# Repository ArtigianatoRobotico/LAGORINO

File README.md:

# LAGORINO
Lagorino is a small didactic robot made in Langhirano (Parma IT) by Stefano Scibilia and developed with the contribute of RoboMakersLab

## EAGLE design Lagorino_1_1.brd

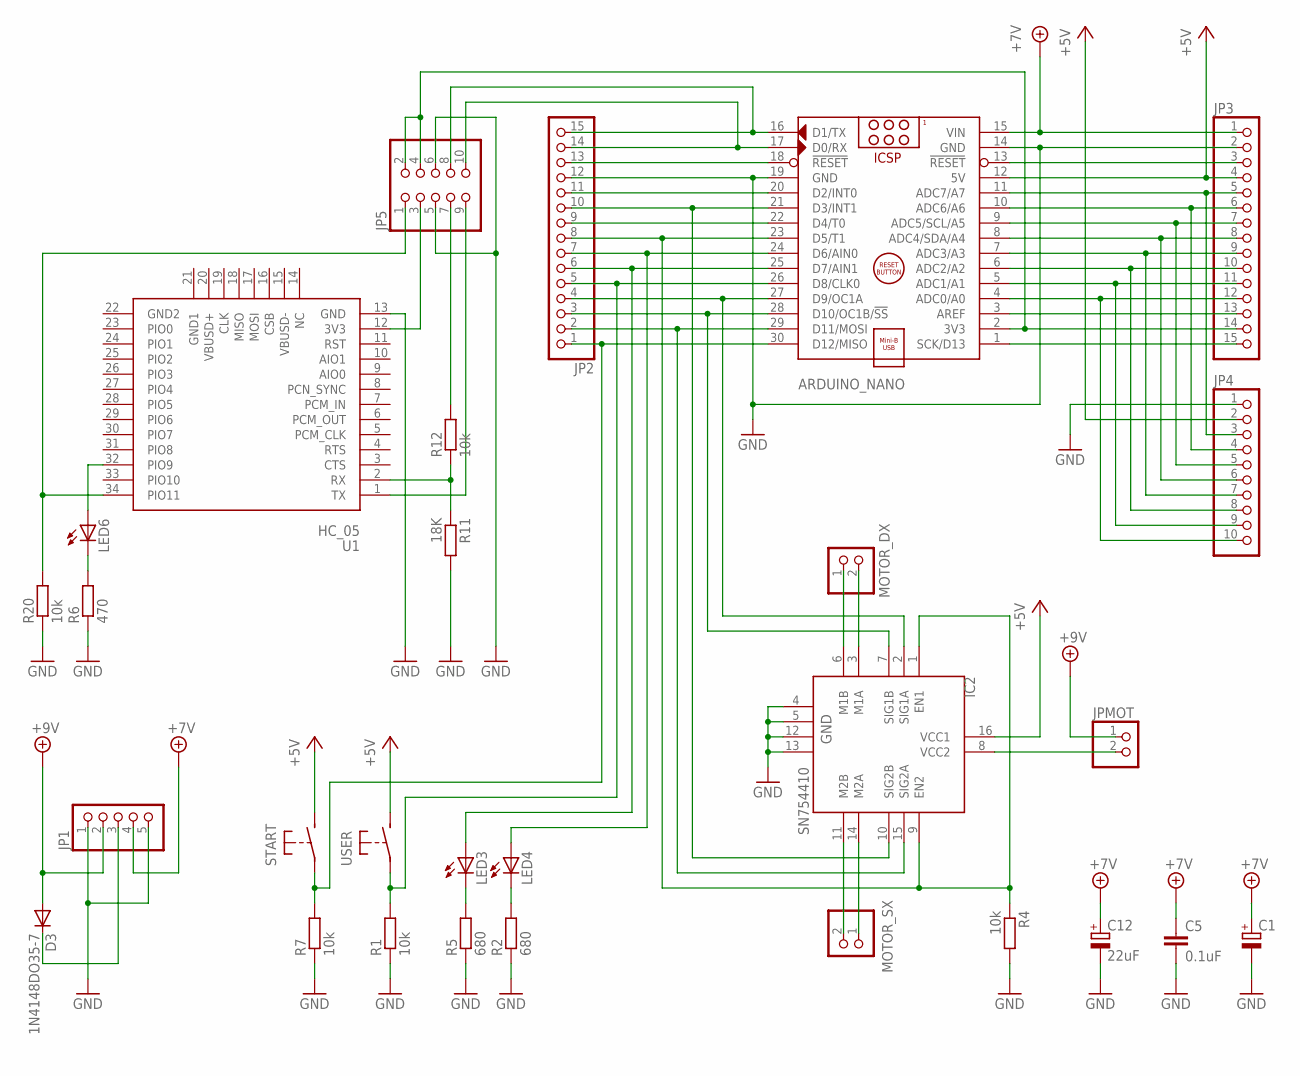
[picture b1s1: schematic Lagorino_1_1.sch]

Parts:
ARDUINO_NANO: ARDUINO_NANO
C1: CPOL-EUE5-6; E5-6
C5: 0.1uF; C0805K
C12: 22uF; A/3216-18W
D3: 1N4148DO35-7; DO35-7
IC2: SN754410; DIP16
JP1: PINHD-1X5; 1X05
JP2, JP3: PINHD-1X15; 1X15
JP4: PINHD-1X10; 1X10
JP5: PINHD-2X5; 2X05
JPMOT: PINHD-1X2; 1X02
LED3, LED4, LED6: LED_E; LED_1206
MOTOR_DX: PINHD-1X2; 1X02
MOTOR_SX: PINHD-1X2; 1X02
R1, R4, R20: 10k; M0805
R2, R5: 680; R0805
R6: 470; R0805
R7, R12: 10k; R0805
R11: 18K; M0805
START: SWITCH-MISC_FSM
U1: HC_05; BLUETOOTH_SMD
USER: SWITCH-MISC_FSM

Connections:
+5V: ARDUINO_NANO.12 (5V), IC2.16 (VCC1), JP3.4, JP4.2, START.P$2 (S), USER.P$2 (S)
+7V: ARDUINO_NANO.15 (VIN), C1.+, C5.1, C12.+, JP1.4, JP3.1
+9V: D3.A, JP1.2, JPMOT.1
GND: ARDUINO_NANO.14 (GND), ARDUINO_NANO.19 (GND), C1.-, C5.2, C12.-, IC2.4, IC2.5, IC2.12, IC2.13, JP1.1, JP1.5, JP2.12, JP3.2, JP4.1, JP5.5, JP5.6, R1.1, R2.1, R4.2, R5.1, R6.1, R7.1, R11.2, R20.1, U1.13 (GND)
unnamed: JP5.7, R12.2
unnamed: JP5.9, U1.1 (TX)
unnamed: IC2.8 (VCC2), JPMOT.2
unnamed: D3.C, JP1.3
unnamed: IC2.6 (M1B), MOTOR_DX.1
unnamed: ARDUINO_NANO.27 (D9/OC1A), IC2.2 (SIG1A), JP2.4
unnamed: ARDUINO_NANO.26 (D8/CLK0), JP2.5, R1.2, USER.P$1
unnamed: ARDUINO_NANO.25 (D7/AIN1), JP2.6, LED3.A
unnamed: ARDUINO_NANO.24 (D6/AIN0), JP2.7, LED4.A
unnamed: IC2.3 (M1A), MOTOR_DX.2
unnamed: ARDUINO_NANO.2 (3V3), JP3.14, JP5.2, JP5.4
unnamed: IC2.11 (M2B), MOTOR_SX.2
unnamed: IC2.14 (M2A), MOTOR_SX.1
unnamed: ARDUINO_NANO.13 (!RESET), JP3.3
unnamed: ARDUINO_NANO.17 (D0/RX), JP2.14, JP5.10
unnamed: ARDUINO_NANO.16 (D1/TX), JP2.15, JP5.8
unnamed: ARDUINO_NANO.29 (D11/MOSI), IC2.15 (SIG2A), JP2.2
unnamed: ARDUINO_NANO.3 (AREF), JP3.13
unnamed: ARDUINO_NANO.11 (ADC7/A7), JP3.5, JP4.3
unnamed: R11.1, R12.1, U1.2 (RX)
unnamed: ARDUINO_NANO.10 (ADC6/A6), JP3.6, JP4.4
unnamed: ARDUINO_NANO.9 (ADC5/SCL/A5), JP3.7, JP4.5
unnamed: ARDUINO_NANO.8 (ADC4/SDA/A4), JP3.8, JP4.6
unnamed: JP5.3, U1.12 (3V3)
unnamed: ARDUINO_NANO.1 (SCK/D13), JP3.15
unnamed: ARDUINO_NANO.7 (ADC3/A3), JP3.9, JP4.7
unnamed: ARDUINO_NANO.6 (ADC2/A2), JP3.10, JP4.8
unnamed: ARDUINO_NANO.5 (ADC1/A1), JP3.11, JP4.9
unnamed: ARDUINO_NANO.4 (ADC0/A0), JP3.12, JP4.10
unnamed: ARDUINO_NANO.18 (!RESET), JP2.13
unnamed: ARDUINO_NANO.20 (D2/INT0), JP2.11
unnamed: LED4.C, R2.2
unnamed: LED3.C, R5.2
unnamed: ARDUINO_NANO.30 (D12/MISO), JP2.1, R7.2, START.P$1
unnamed: ARDUINO_NANO.22 (D4/T0), JP2.9
unnamed: ARDUINO_NANO.21 (D3/INT1), IC2.10 (SIG2B), JP2.10
unnamed: ARDUINO_NANO.28 (D10/OC1B/!SS), IC2.7 (SIG1B), JP2.3
unnamed: ARDUINO_NANO.23 (D5/T1), IC2.1 (EN1), IC2.9 (EN2), JP2.8, R4.1
unnamed: LED6.C, R6.2
unnamed: LED6.A, U1.32 (PIO9)
unnamed: JP5.1, R20.2, U1.34 (PIO11)

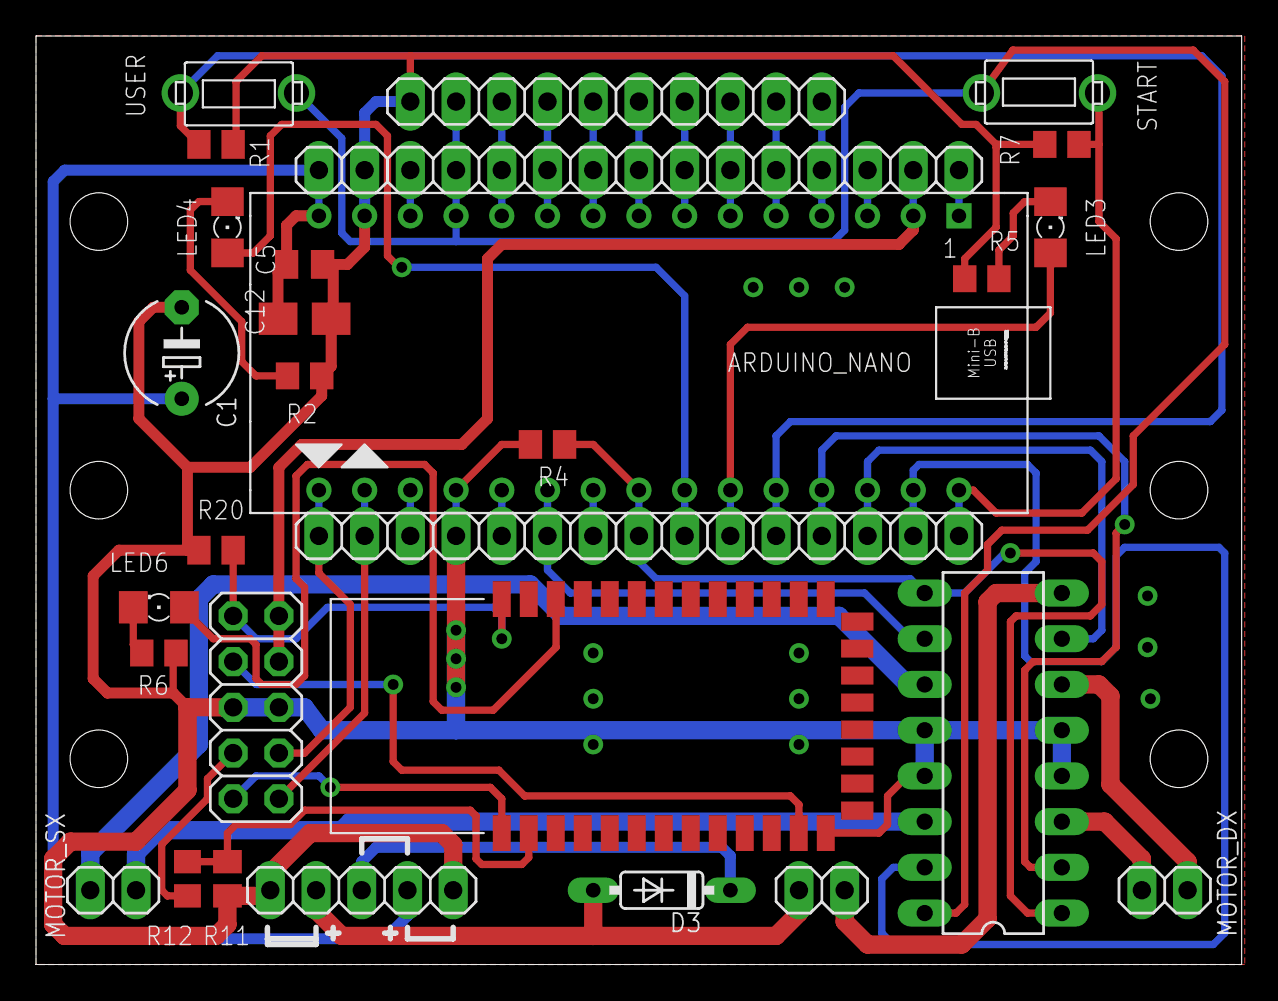
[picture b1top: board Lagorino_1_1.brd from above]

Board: 2 copper layers, 67.0 x 51.6 mm, 29 parts (0 on the bottom side), 45 nets.

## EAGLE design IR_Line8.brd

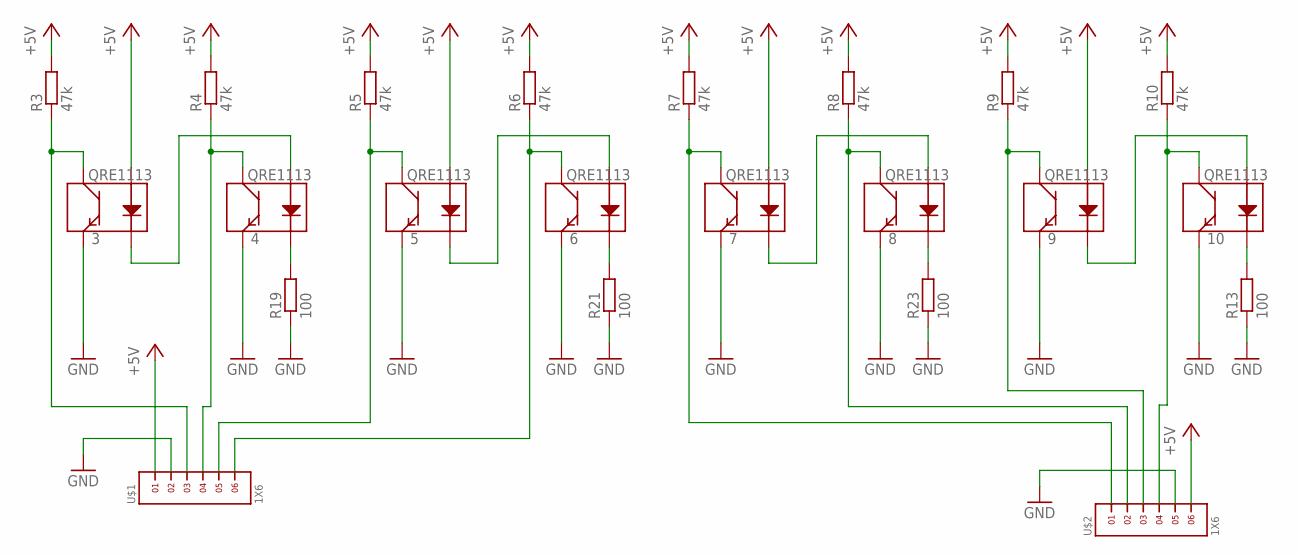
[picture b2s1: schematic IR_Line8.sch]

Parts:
3, 4, 5, 6, 7, 8, 9, 10: QRE1113
R3, R4, R5, R6, R7, R8, R9, R10: 47k; R0805
R13, R19, R21, R23: 100; R0805
U$1, U$2: 1X6

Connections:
+5V: 3.1 (A), 5.1 (A), 7.1 (A), 9.1 (A), R3.2, R4.2, R5.2, R6.2, R7.2, R8.2, R9.2, R10.2, U$1.1, U$2.6
GND: 3.4 (E), 4.4 (E), 5.4 (E), 6.4 (E), 7.4 (E), 8.4 (E), 9.4 (E), 10.4 (E), R13.1, R19.1, R21.1, R23.1, U$1.2, U$2.5
unnamed: 10.3 (C), R10.1, U$2.4
unnamed: 6.3 (C), R6.1, U$1.6
unnamed: 3.2 (K), 4.1 (A)
unnamed: 5.3 (C), R5.1, U$1.5
unnamed: 4.3 (C), R4.1, U$1.4
unnamed: 3.3 (C), R3.1, U$1.3
unnamed: 5.2 (K), 6.1 (A)
unnamed: 7.2 (K), 8.1 (A)
unnamed: 4.2 (K), R19.2
unnamed: 9.3 (C), R9.1, U$2.3
unnamed: 10.2 (K), R13.2
unnamed: 9.2 (K), 10.1 (A)
unnamed: 6.2 (K), R21.2
unnamed: 7.3 (C), R7.1, U$2.1
unnamed: 8.2 (K), R23.2
unnamed: 8.3 (C), R8.1, U$2.2

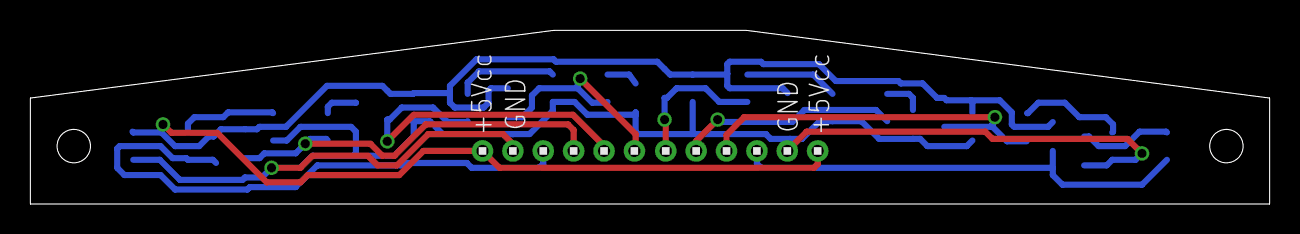
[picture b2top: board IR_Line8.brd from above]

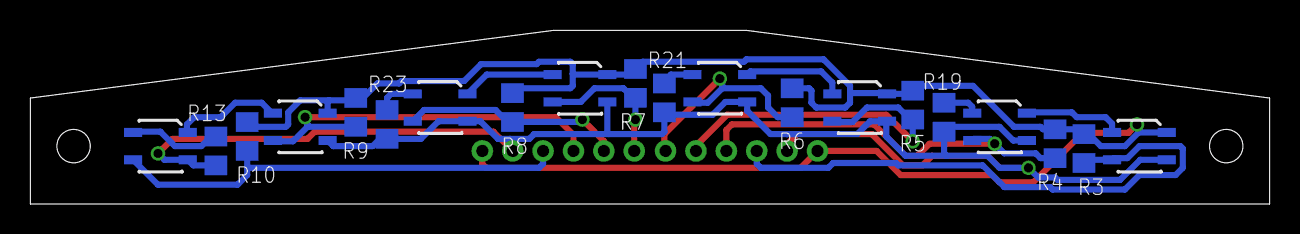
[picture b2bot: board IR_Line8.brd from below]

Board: 2 copper layers, 81.6 x 11.4 mm, 22 parts (20 on the bottom side), 18 nets.
